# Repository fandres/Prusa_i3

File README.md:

This repository is possibly outdated
Este Repositorio se probablemente se encuentra desactualizado

Repository migrated to https://gitlab.com/fandres323/Prusa_i3
Repositorio migrado a https://gitlab.com/fandres323/Prusa_i3

# Prusa_i3
============

License 
======

[Creative Commons Attribution-ShareAlike 4.0 International License](http://creativecommons.org/licenses/by-sa/4.0/)

Attributions
============
See commit details to find the authors of each Part.
- @fandres

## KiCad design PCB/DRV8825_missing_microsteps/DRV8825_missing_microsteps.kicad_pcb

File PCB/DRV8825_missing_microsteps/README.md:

## DRV8825 Missing Microsteps
DRV8825 Missing Steps

## BOM 
Ref | Qty | Value | Footprint 
--- | --- | ----- | --------
D1 D2 D3 D4  | 4 | S3G SMC DO-214AB 
J1 J2  | 2 | Conn_01x04 

# Order from OSH Park, $3 x2.85 

<a href="https://oshpark.com/shared_projects/WslGSema"></img></a>

# Images

# License 
======

[MIT License](/PCB/DRV8825_missing_microsteps/Images/LICENCE)

# Attributions
============
See commit details to find the authors of each Part.
- @fandres

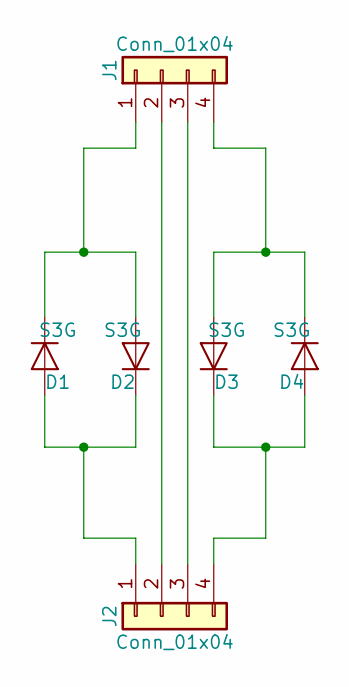
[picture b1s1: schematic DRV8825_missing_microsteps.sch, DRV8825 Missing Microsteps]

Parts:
D1, D2, D3, D4: S3G; DO-214AB
J1, J2: Conn_01x04; Pin_Header_Straight_1x04

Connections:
unnamed: D1.1 (K), D2.2 (A), J1.1
unnamed: D1.2 (A), D2.1 (K), J2.1
unnamed: D3.1 (K), D4.2 (A), J2.4
unnamed: D3.2 (A), D4.1 (K), J1.4
unnamed: J1.2, J2.2
unnamed: J1.3, J2.3

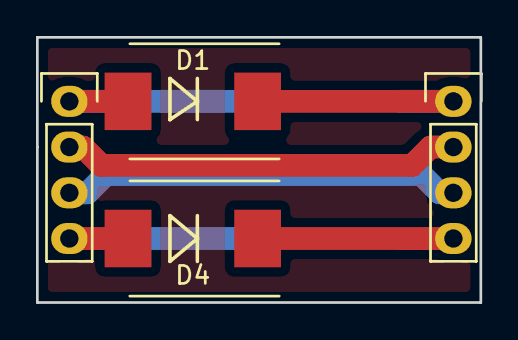
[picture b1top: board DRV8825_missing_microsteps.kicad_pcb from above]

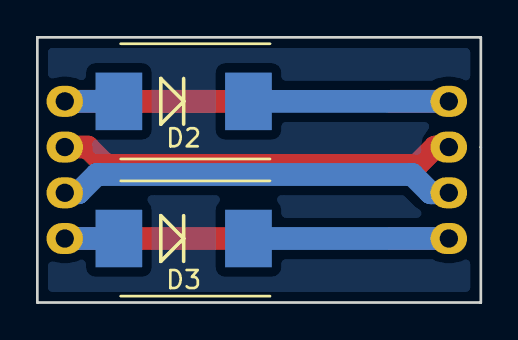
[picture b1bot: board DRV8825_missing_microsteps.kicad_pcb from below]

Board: 2 copper layers, 24.6 x 14.7 mm, 6 parts (2 on the bottom side), 6 nets.

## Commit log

2017-09-01 Model Endstop Y
2017-09-01 Added Config Firmware Marlin
2017-09-01 Added list of parts and costs
2017-09-01 Added Config Slic3r
2017-09-01 PCB: DRV8825 Missing Microsteps
2017-09-15 Update Profiles (Quality)
2017-09-15 Update Speed Z
2017-10-06 Autotuning Bed And Hotend
2017-10-10 Ajusts 3Points Added SD Card
2017-10-10 Fork Marlin 1.1.6
2017-10-10 Fasteners security: BED
2017-10-19 Correct
2017-11-05 Added Image and LICENCE
2017-12-27 Update config tested - Retraction - Temp Off
2018-01-29 Added firmware marlin 1.1.8
2018-01-29 Added two new higher speed configurations
2018-02-20 Added Config for BLTouch
2018-02-26 Added Components: BLTOuch, DRV8825 missing and others
2018-02-26 Ajust: Speed Bridges Suport And others
2018-06-12 Update README.md
    Repository migrated to https://gitlab.com/fandres323/Prusa_i3
